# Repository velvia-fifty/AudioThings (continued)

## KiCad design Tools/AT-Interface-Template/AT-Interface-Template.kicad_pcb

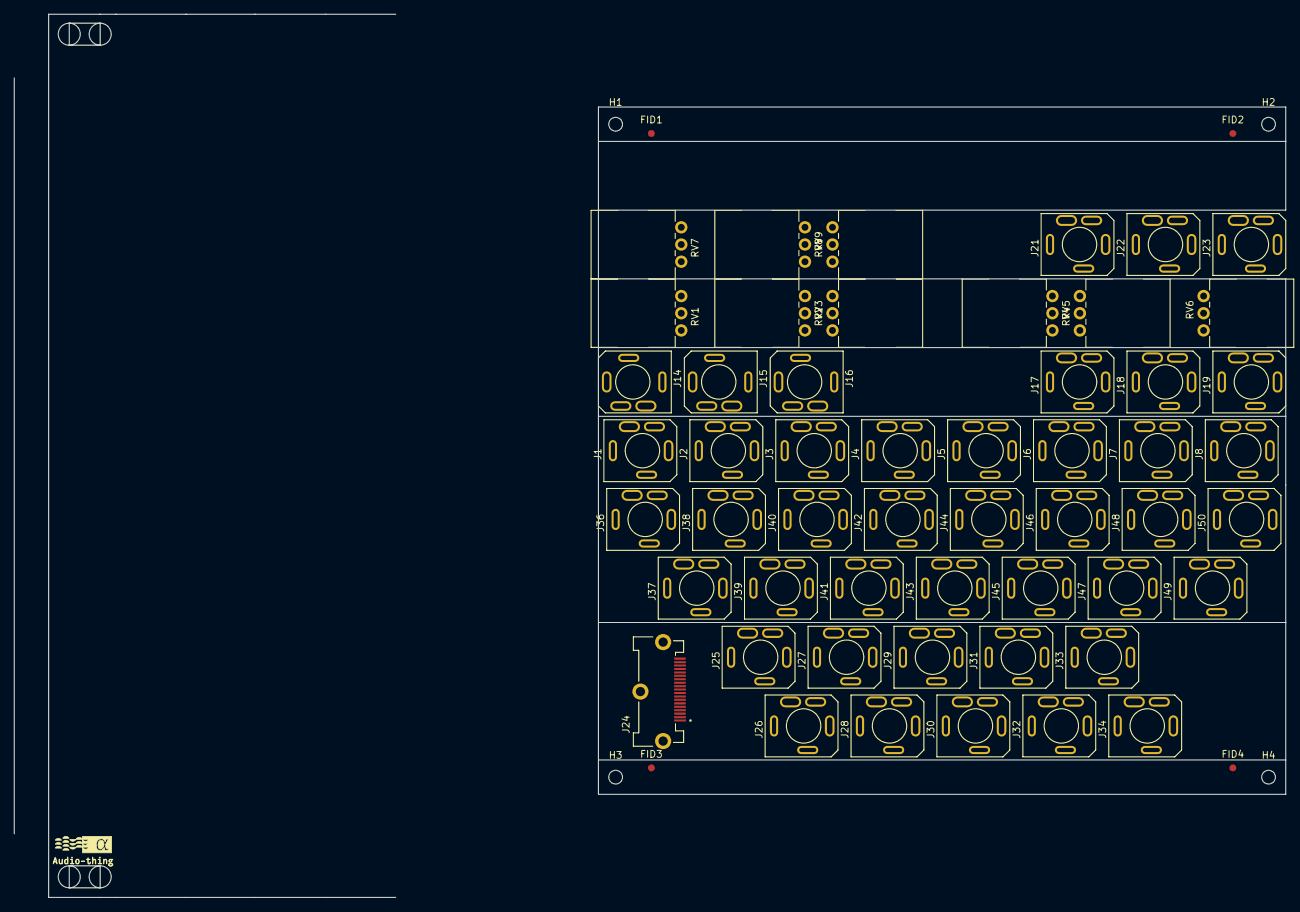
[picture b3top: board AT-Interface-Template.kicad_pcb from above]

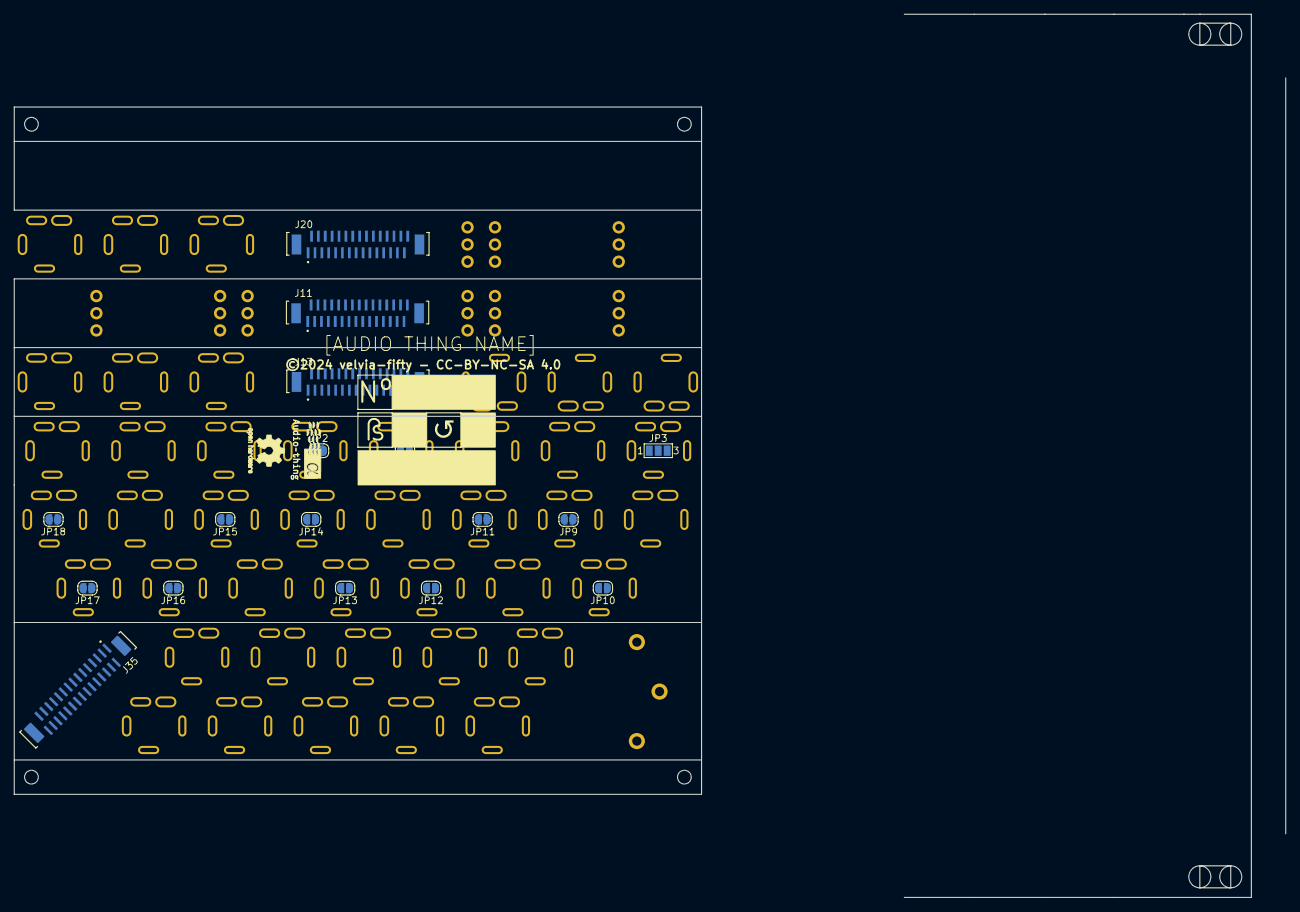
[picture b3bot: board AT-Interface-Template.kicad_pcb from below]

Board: 2 copper layers, 100.0 x 100.0 mm, 77 parts (17 on the bottom side), 102 nets, no tracks yet.

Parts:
FID1, FID2, FID3, FID4: Fiducial; Fiducial_1mm_Mask2mm
H1, H2, H3, H4: Tooling; MountingHole_2mm
J1, J2, J3, J4, J5, J6, J7, J8, J14, J15, J16, J17, J18, J19, J21, J22, J23, J36, J39, J42, J45, J48: IN; SJ3-3505
J11, J13, J20, J35: INT; ffc-30-v-TE_3-1734742-0
J24: HDMI; HDMI-v-PHOENIX_1332073
J25: 1; SJ3-3505
J26: 2; SJ3-3505
J27: 3; SJ3-3505
J28: 4; SJ3-3505
J29: 5; SJ3-3505
J30: 6; SJ3-3505
J31: 7; SJ3-3505
J32: 8; SJ3-3505
J33: 9; SJ3-3505
J34: M; SJ3-3505
J37, J40, J43, J46, J49: LEFT; SJ3-3505
J38, J41, J44, J47, J50: RIGHT; SJ3-3505
JP1: JOIN L; SolderJumper-2_P1.3mm_Open_RoundedPad1.0x1.5mm
JP2: JOIN R; SolderJumper-2_P1.3mm_Open_RoundedPad1.0x1.5mm
JP3: STEREO CONF; SolderJumper-3_P1.3mm_Open_Pad1.0x1.5mm_NumberLabels
JP9, JP10, JP11, JP12, JP13, JP14, JP15, JP16, JP17, JP18: DMONO; SolderJumper-2_P1.3mm_Open_RoundedPad1.0x1.5mm
RV1, RV2, RV3, RV4, RV5, RV6: PTV09 Pot V; 2HP_PTV09A-1_Single_Vertical
RV7, RV8, RV9: PTV09 Pot HZ; 2HP_PTV09A-1_Single_Vertical

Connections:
+12v: J11.1, J11.2, J13.1, J13.2, J20.1, J20.2, J35.1, J35.2
-12v: J11.29, J11.30, J13.29, J13.30, J20.29, J20.30, J35.29, J35.30
/ExtraMult/GND: J1.S, J2.S, J3.S, J4.S, J5.S, J6.S, J7.S, J8.S
/HDMI/R1: J24.2, J25.R, J35.5
/HDMI/R2: J24.4, J26.R, J35.9
/HDMI/R3: J24.6, J27.R, J35.13
/HDMI/R4: J24.8, J28.R, J35.16
/HDMI/R5: J24.10, J29.R, J35.20
/HDMI/R6: J24.12, J30.R, J35.24
/HDMI/R7: J24.14, J31.R
/HDMI/R8: J24.16, J32.R
/HDMI/R9: J24.18, J33.R
/HDMI/T1: J24.1, J25.T, J35.6
/HDMI/T2: J24.3, J26.T, J35.10
/HDMI/T3: J24.5, J27.T, J35.14
/HDMI/T4: J24.7, J28.T, J35.17
/HDMI/T5: J24.9, J29.T, J35.21
/HDMI/T6: J24.11, J30.T, J35.25
/HDMI/T7: J24.13, J31.T
/HDMI/T8: J24.15, J32.T
/HDMI/T9: J24.17, J33.T
/HDMI/T10: J24.19, J34.T
/Jacks/INT 1 - A: J13.5, J14.R
/Jacks/INT 1 - B: J13.6, J14.T
/Jacks/INT 1 - C: J13.7, J14.TN
/Jacks/INT 2 - A: J13.9, J15.R
/Jacks/INT 2 - B: J13.10, J15.T
/Jacks/INT 2 - C: J13.11, J15.TN
/Jacks/INT 3 - A: J13.13, J16.R
/Jacks/INT 3 - B: J13.14, J16.T
/Jacks/INT 3 - C: J13.15, J16.TN
/Jacks/INT 4 - A: J13.16, J17.R
/Jacks/INT 4 - B: J13.17, J17.T
/Jacks/INT 4 - C: J13.18, J17.TN
/Jacks/INT 5 - A: J13.20, J18.R
/Jacks/INT 5 - B: J13.21, J18.T
/Jacks/INT 5 - C: J13.22, J18.TN
/Jacks/INT 6 - A: J13.24, J19.R
/Jacks/INT 6 - B: J13.25, J19.T
/Jacks/INT 6 - C: J13.26, J19.TN
/Pot+Jack/INT 1 - A: J20.5, RV7.1
/Pot+Jack/INT 1 - B: J20.6, RV7.2
/Pot+Jack/INT 1 - C: J20.7, RV7.3
/Pot+Jack/INT 2 - A: J20.9, RV8.1
/Pot+Jack/INT 2 - B: J20.10, RV8.2
/Pot+Jack/INT 2 - C: J20.11, RV8.3
/Pot+Jack/INT 3 - A: J20.13, RV9.1
/Pot+Jack/INT 3 - B: J20.14, RV9.2
/Pot+Jack/INT 3 - C: J20.15, RV9.3
/Pot+Jack/INT 4 - A: J20.16, J21.R
/Pot+Jack/INT 4 - B: J20.17, J21.T
/Pot+Jack/INT 4 - C: J20.18, J21.TN
/Pot+Jack/INT 5 - A: J20.20, J22.R
/Pot+Jack/INT 5 - B: J20.21, J22.T
/Pot+Jack/INT 5 - C: J20.22, J22.TN
/Pot+Jack/INT 6 - A: J20.24, J23.R
/Pot+Jack/INT 6 - B: J20.25, J23.T
/Pot+Jack/INT 6 - C: J20.26, J23.TN
/Pots/INT 1 - A: J11.5, RV1.1
/Pots/INT 1 - B: J11.6, RV1.2
/Pots/INT 1 - C: J11.7, RV1.3
/Pots/INT 2 - A: J11.9, RV2.1
/Pots/INT 2 - B: J11.10, RV2.2
/Pots/INT 2 - C: J11.11, RV2.3
/Pots/INT 3 - A: J11.13, RV3.1
/Pots/INT 3 - B: J11.14, RV3.2
/Pots/INT 3 - C: J11.15, RV3.3
/Pots/INT 4 - A: J11.16, RV4.1
/Pots/INT 4 - B: J11.17, RV4.2
/Pots/INT 4 - C: J11.18, RV4.3
/Pots/INT 5 - A: J11.20, RV5.1
/Pots/INT 5 - B: J11.21, RV5.2
/Pots/INT 5 - C: J11.22, RV5.3
/Pots/INT 6 - A: J11.24, RV6.1
/Pots/INT 6 - B: J11.25, RV6.2
/Pots/INT 6 - C: J11.26, RV6.3
GND: J11.3, J11.4, J11.8, J11.12, J11.19, J11.23, J11.27, J11.28, J11.S1, J13.3, J13.4, J13.8, J13.12, J13.19, J13.23, J13.27, J13.28, J13.S1, J20.3, J20.4, J20.8, J20.12, J20.19, J20.23, J20.27, J20.28, J20.S1, J24.SH1, J24.SH2, J24.SH3, J25.S, J26.S, J27.S, J28.S, J29.S, J30.S, J31.S, J32.S, J33.S, J34.S, J35.3, J35.4, J35.8, J35.12, J35.19, J35.23, J35.27, J35.28, J35.S1, J36.S, J37.S, J38.S, J39.S, J40.S, J41.S, J42.S, J43.S, J44.S, J45.S, J46.S, J47.S, J48.S, J49.S, J50.S
unnamed: J5.T, J6.T, J7.T, J8.T, JP1.1 (A), JP3.1 (A)
unnamed: J1.T, J2.T, J3.T, J4.T, JP1.2 (B)
unnamed: J5.R, J6.R, J7.R, J8.R, JP2.1 (A)
unnamed: J2.R, J3.R, J4.R, JP2.2 (B), JP3.3 (B)
unnamed: J1.R, JP3.2 (C)
unnamed: J36.R, J38.T, JP9.1 (A)
unnamed: J38.R, JP9.2 (B)
unnamed: J36.T, J37.T, JP10.1 (A)
unnamed: J37.R, JP10.2 (B)
unnamed: J39.T, J40.T, JP11.1 (A)
unnamed: J40.R, JP11.2 (B)
unnamed: J39.R, J41.T, JP12.1 (A)
unnamed: J41.R, JP12.2 (B)
unnamed: J42.T, J43.T, JP13.1 (A)
unnamed: J43.R, JP13.2 (B)
unnamed: J42.R, J44.T, JP14.1 (A)
unnamed: J44.R, JP14.2 (B)
unnamed: J45.T, J46.T, JP15.1 (A)
unnamed: J46.R, JP15.2 (B)
unnamed: J45.R, J47.T, JP16.1 (A)
unnamed: J47.R, JP16.2 (B)
unnamed: J48.T, J49.T, JP17.1 (A)
unnamed: J49.R, JP17.2 (B)
unnamed: J48.R, J50.T, JP18.1 (A)
unnamed: J50.R, JP18.2 (B)

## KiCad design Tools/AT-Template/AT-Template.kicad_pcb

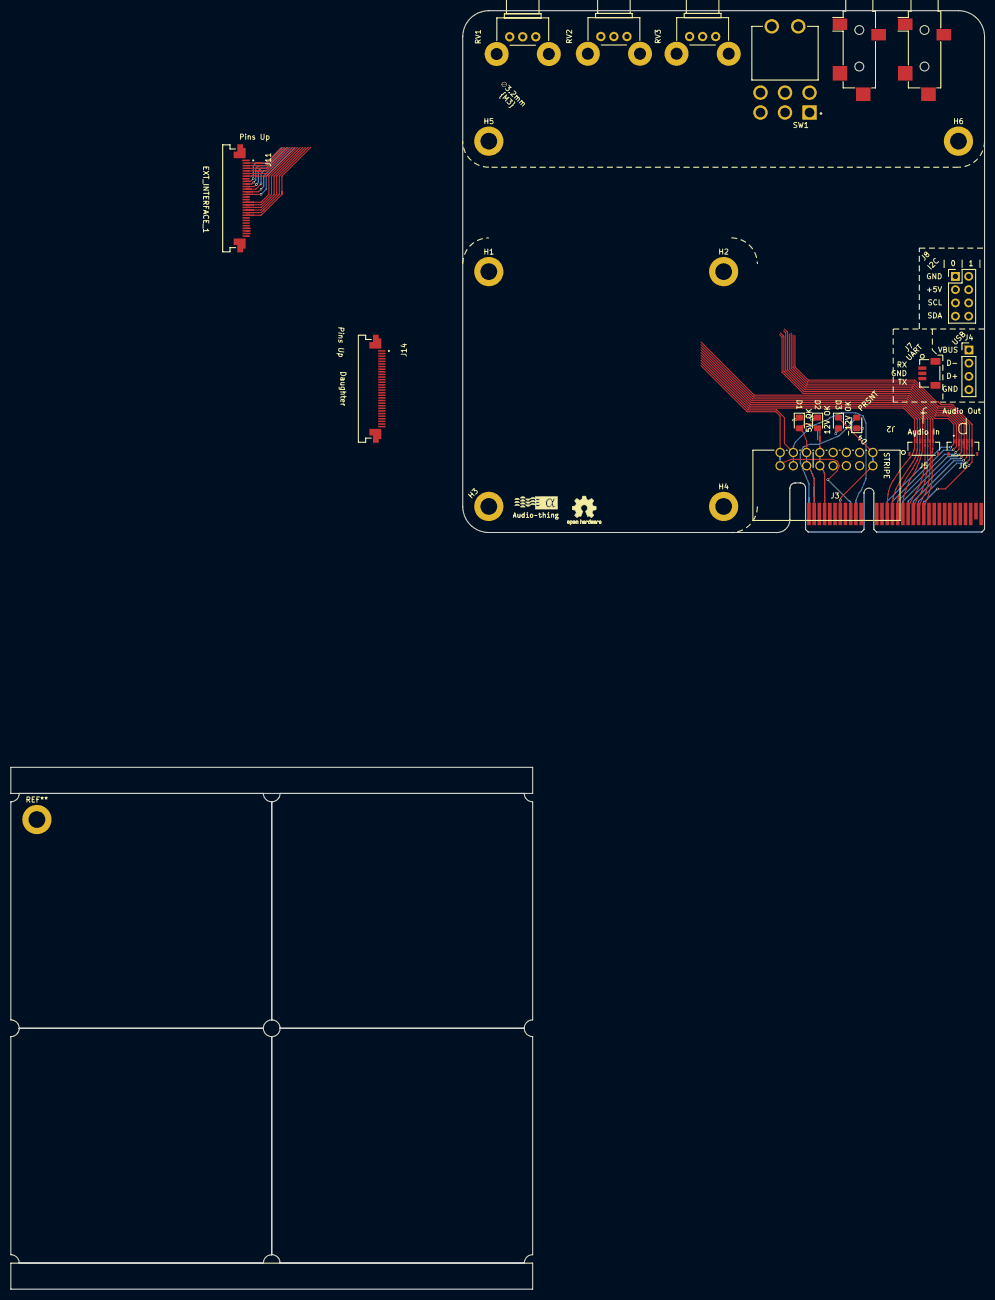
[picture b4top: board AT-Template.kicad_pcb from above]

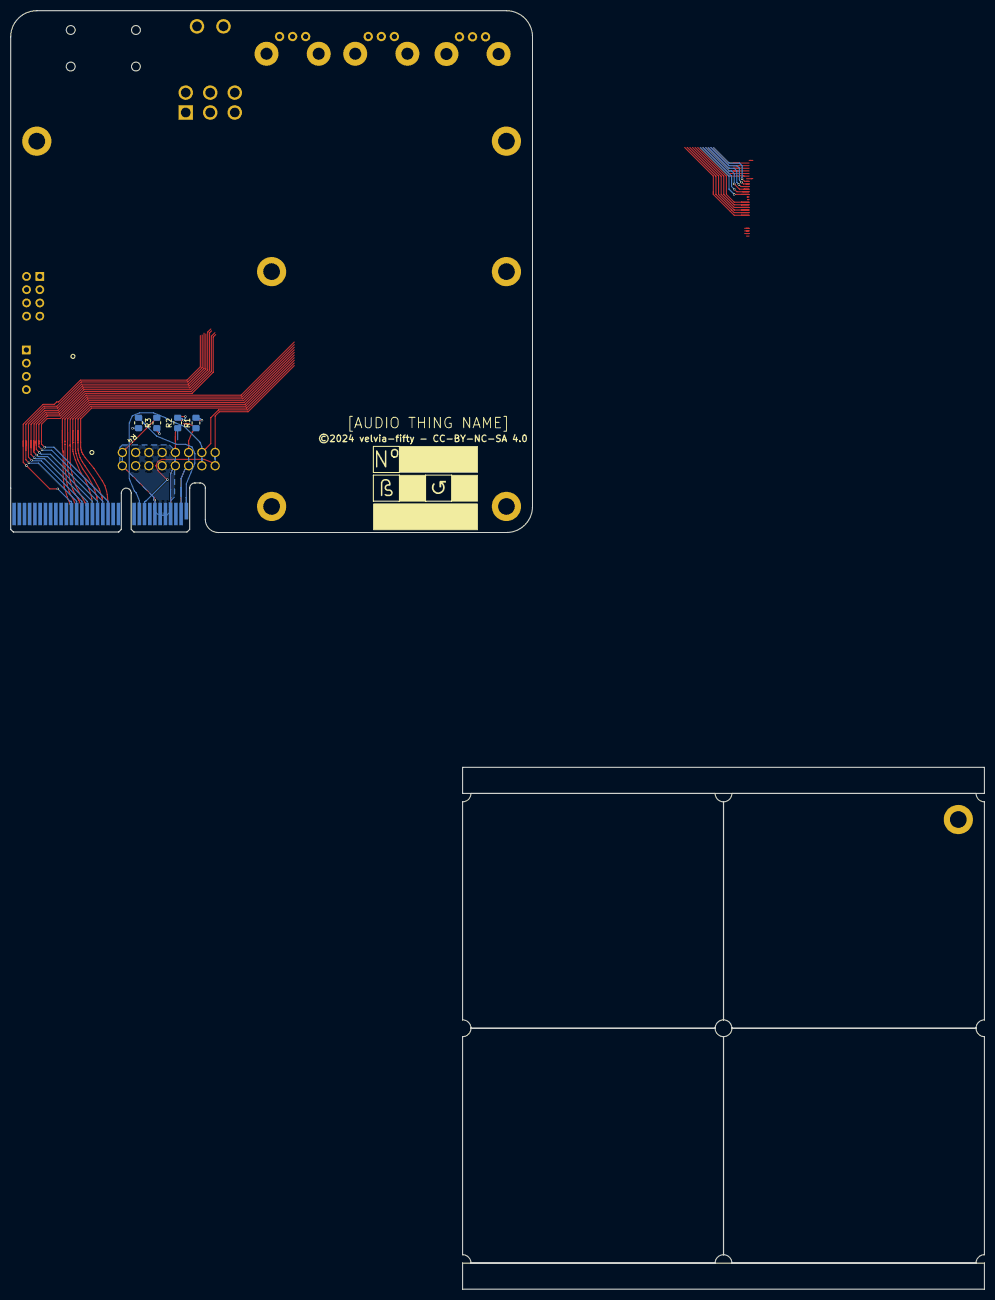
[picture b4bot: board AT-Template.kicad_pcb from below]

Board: 2 copper layers, 100.0 x 100.0 mm, 29 parts (4 on the bottom side), 29 nets.

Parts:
D1: 5V OK; LED_0805_2012Metric_Pad1.15x1.40mm_HandSolder
D2: 12V OK; LED_0805_2012Metric_Pad1.15x1.40mm_HandSolder
D3: -12V OK; LED_0805_2012Metric_Pad1.15x1.40mm_HandSolder
D4: PRSNT; LED_0805_2012Metric_Pad1.15x1.40mm_HandSolder
H1, H2, H3, H4, H5, H6: M3; MountingHole_3.2mm_M3_DIN965_Pad
J2: OPT EURO; EURORACK Right Angle
J3: BUS_PCIexpress_x4
J4: USB; PinHeader_1x04_P2.54mm_Vertical
J5: Audio In; AMPHENOL_F33B-1A7Q1-E8C08
J6: Audio Out; AMPHENOL_F33B-1A7Q1-E8C08
J7: UART; CONN_BM03B-SRSS-TBLFSN_JST
J8: I2C; PinHeader_2x04_P2.54mm_Vertical
J9, J10: Stereo Jack - SMD HZ; SMD_STEREO_CUI_SJ-3524-SMT_Horizontal
J11: EXT_INTERFACE_1; AMPHENOL_SFV30R-4STE1HLF - FFC - 30 RA
J14: Daughter; AMPHENOL_SFV30R-4STE1HLF - FFC - 30 RA
R1, R4: 150; R_0805_2012Metric_Pad1.20x1.40mm_HandSolder
R2, R3: 500; R_0805_2012Metric_Pad1.20x1.40mm_HandSolder
RV1, RV2, RV3: PTV09 Pot HZ; Potentiometer_Bourns_PTV09A-2_Single_Horizontal
SW1: Micro Toggle; DPDT Micro SW_1825138-7

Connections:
+5V: D1.2 (A), J2.11, J2.12, J3.A2 (+5V), J3.B2 (+5V), J8.3, J8.4
+12V: D2.2 (A), J2.9, J2.10, J3.A4 (+12V), J3.B4 (+12V)
-12V: D3.1 (K), J2.1, J2.2, J3.A7 (-12V), J3.B7 (-12V)
/Bus/CON_CV: J2.13, J2.14, J3.A10 (EURO_CV)
/Bus/CON_GATE: J2.15, J2.16, J3.A9 (EURO_GATE)
/Bus/I2C0_SCL: J3.B23 (I2C0_SCL), J8.5
/Bus/I2C0_SDA: J3.A24 (I2C0_SDA), J8.7
/Bus/I2C1_SCL: J3.A27 (I2C1_SCL), J8.6
/Bus/I2C1_SDA: J3.B27 (I2C1_SDA), J8.8
/Bus/USB_D+: J3.B12 (USB_D+), J4.3
GND: J2.3, J2.4, J2.5, J2.6, J2.7, J2.8, J3.A3 (GND), J3.A5 (GND), J3.A6 (GND), J3.A8 (GND), J3.A11 (GND), J3.A15 (GND), J3.A17 (GND), J3.A19 (GND), J3.A21 (GND), J3.A23 (GND), J3.A26 (GND), J3.B1 (GND), J3.B3 (GND), J3.B5 (GND), J3.B6 (GND), J3.B8 (GND), J3.B11 (GND), J3.B13 (GND), J3.B14 (GND), J3.B16 (GND), J3.B18 (GND), J3.B20 (GND), J3.B26 (GND), J3.B32 (GND), J4.4, J5.1, J5.3, J5.5, J5.7, J6.2, J6.4, J6.6, J6.8, J7.2, J8.1, J8.2, J11.1, J11.8, J11.15, J11.16, J11.23, J11.30, R1.1, R2.1, R3.2
unnamed: D1.1 (K), R1.2
unnamed: D2.1 (K), R2.2
unnamed: D3.2 (A), R3.1
unnamed: D4.2 (A), J3.B31 (PRSNT_B)
unnamed: D4.1 (K), R4.2
unnamed: J3.B15 (Audio_In_A), J5.2
unnamed: J3.B17 (Audio_In_B), J5.4
unnamed: J3.B19 (Audio_In_C), J5.6
unnamed: J3.B21 (Audio_In_D), J5.8
unnamed: J3.A14 (Audio_Out_A), J6.1
unnamed: J3.A16 (Audio_Out_B), J6.3
unnamed: J3.A18 (Audio_Out_C), J6.5
unnamed: J3.A20 (Audio_Out_D), J6.7
unnamed: J3.A1 (PRSNT_A), R4.1
unnamed: J3.B22 (UART_RX), J7.1
unnamed: J3.A22 (UART_TX), J7.3
unnamed: J3.A12 (USB_5V), J4.1
unnamed: J3.A13 (USB_D-), J4.2

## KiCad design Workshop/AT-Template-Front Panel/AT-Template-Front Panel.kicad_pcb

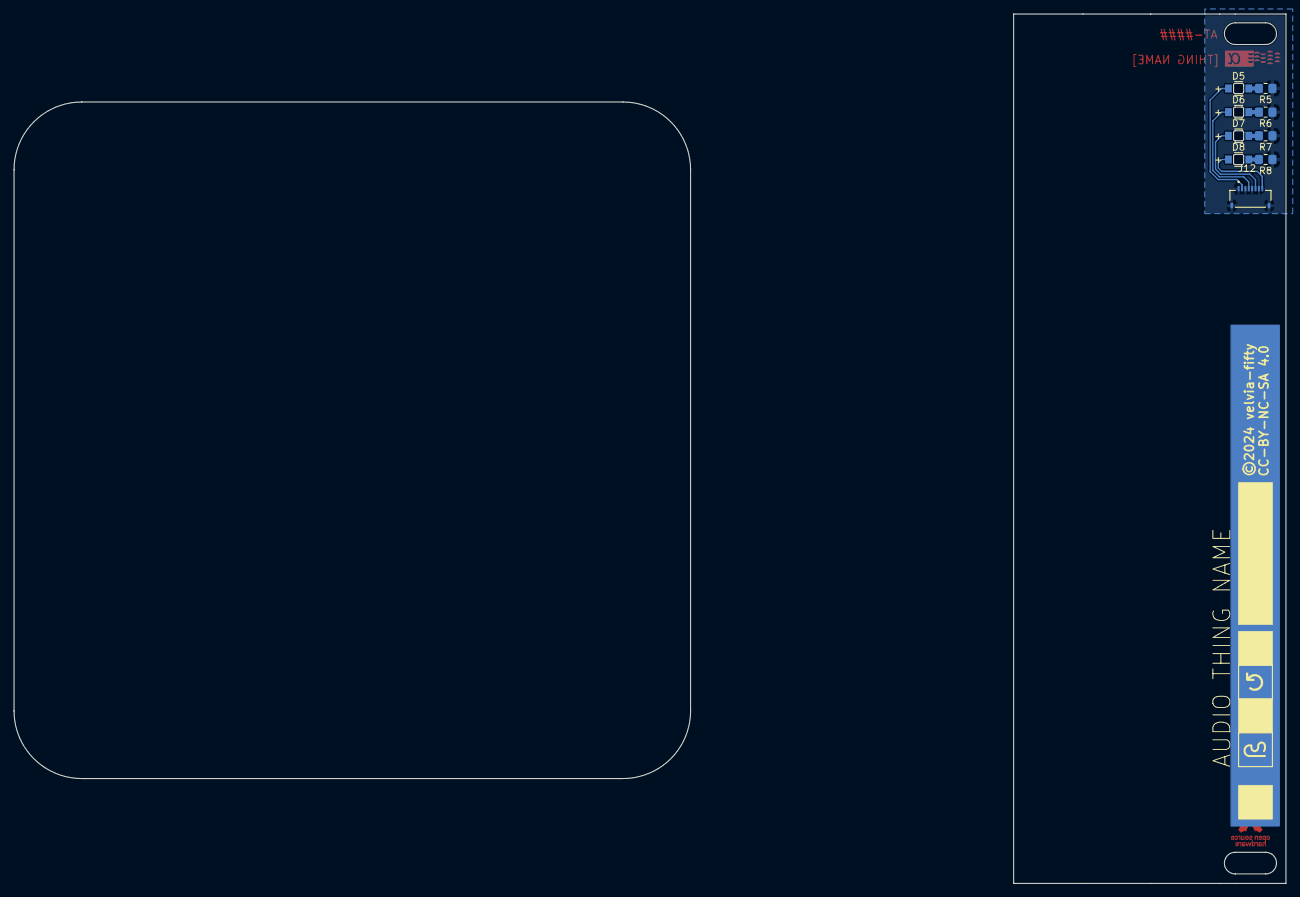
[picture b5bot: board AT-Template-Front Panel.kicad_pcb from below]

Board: 4 copper layers, 40.2 x 128.5 mm, 9 parts (5 on the bottom side), 9 nets.

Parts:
D5: LED (Red); WL-SMRD_1205
D6: LED (Yellow); WL-SMRD_1205
D7: LED (Green); WL-SMRD_1205
D8: LED (Blue); WL-SMRD_1205
J12: FRONT PANEL MAGIC; AMPHENOL_F33B-1A7Q1-E8C08
R5, R6, R7: 150R; R_0805_2012Metric_Pad1.20x1.40mm_HandSolder
R8: 100R; R_0805_2012Metric_Pad1.20x1.40mm_HandSolder

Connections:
GND: J12.1, J12.3, J12.5, J12.7, J12.SH1, J12.SH2, R5.1, R6.1, R7.1, R8.1
LED BLU: D8.2 (A), J12.8
LED GRN: D7.2 (A), J12.6
LED RED: D5.2 (A), J12.2
LED YLW: D6.2 (A), J12.4
unnamed: D5.1 (K), R5.2
unnamed: D6.1 (K), R6.2
unnamed: D7.1 (K), R7.2
unnamed: D8.1 (K), R8.2

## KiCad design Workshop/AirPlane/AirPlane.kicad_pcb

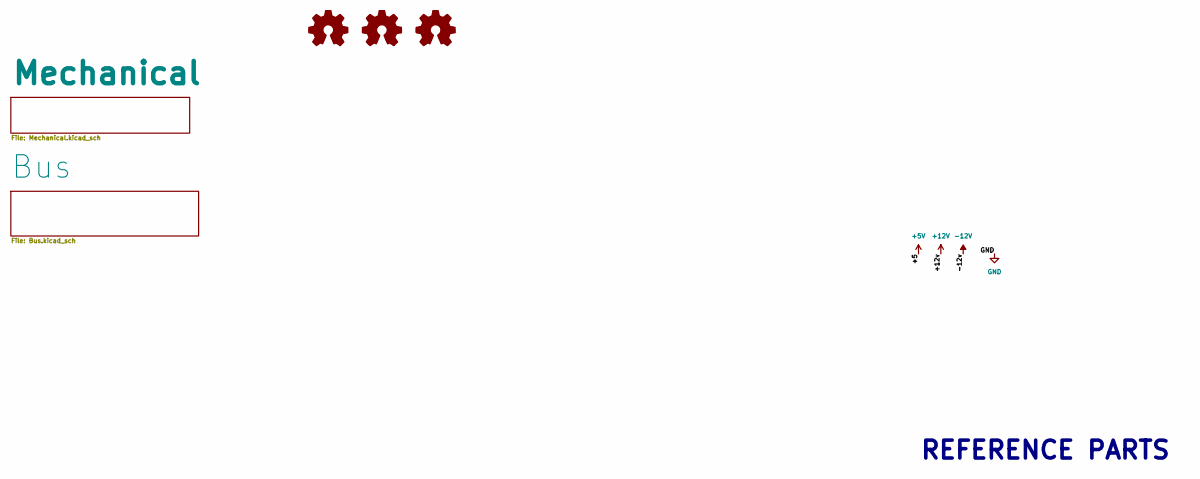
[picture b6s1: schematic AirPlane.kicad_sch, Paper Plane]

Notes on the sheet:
REFERENCE PARTS

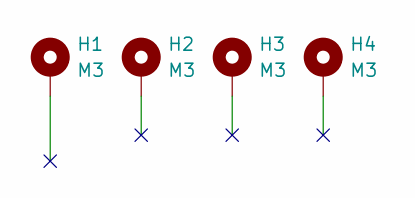
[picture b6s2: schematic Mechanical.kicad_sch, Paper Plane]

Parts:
H1, H2, H3, H4: M3; MountingHole_3.2mm_M3_DIN965_Pad

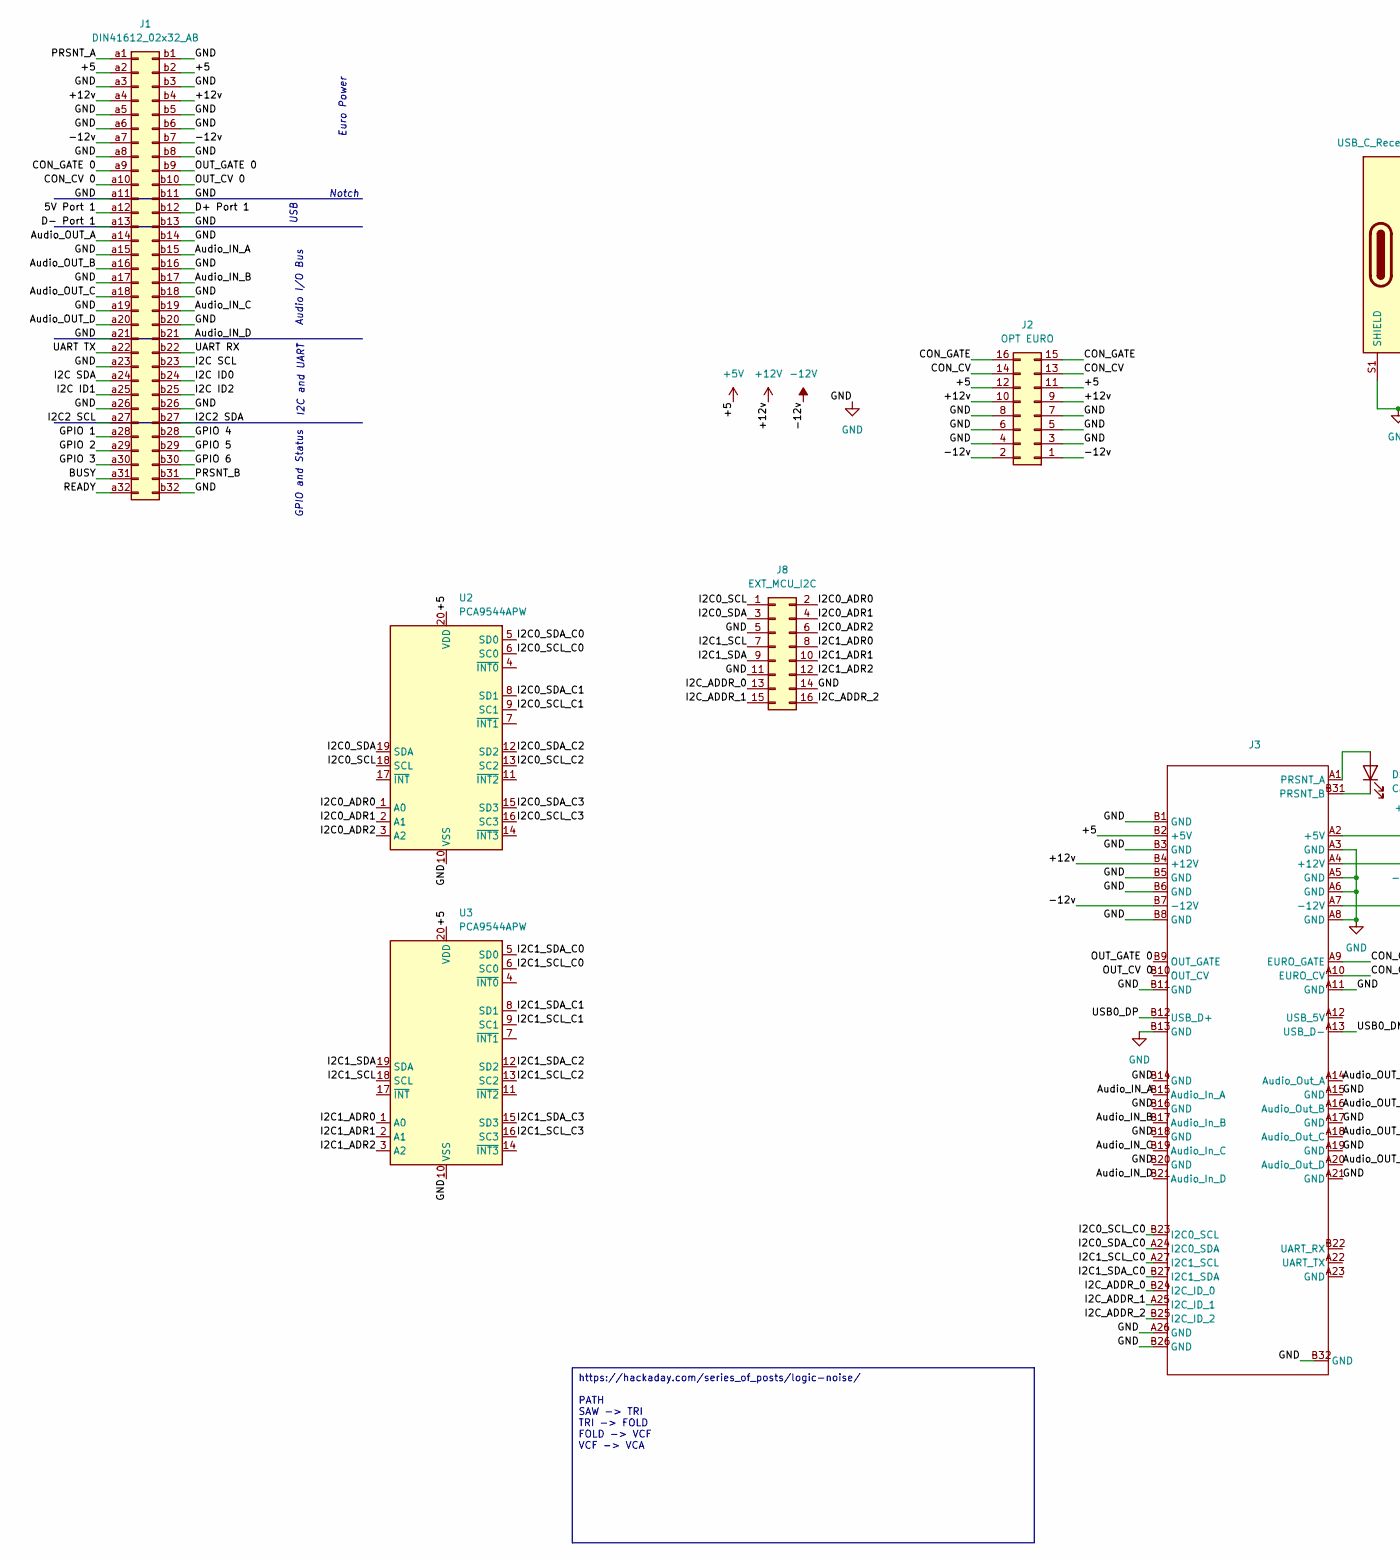
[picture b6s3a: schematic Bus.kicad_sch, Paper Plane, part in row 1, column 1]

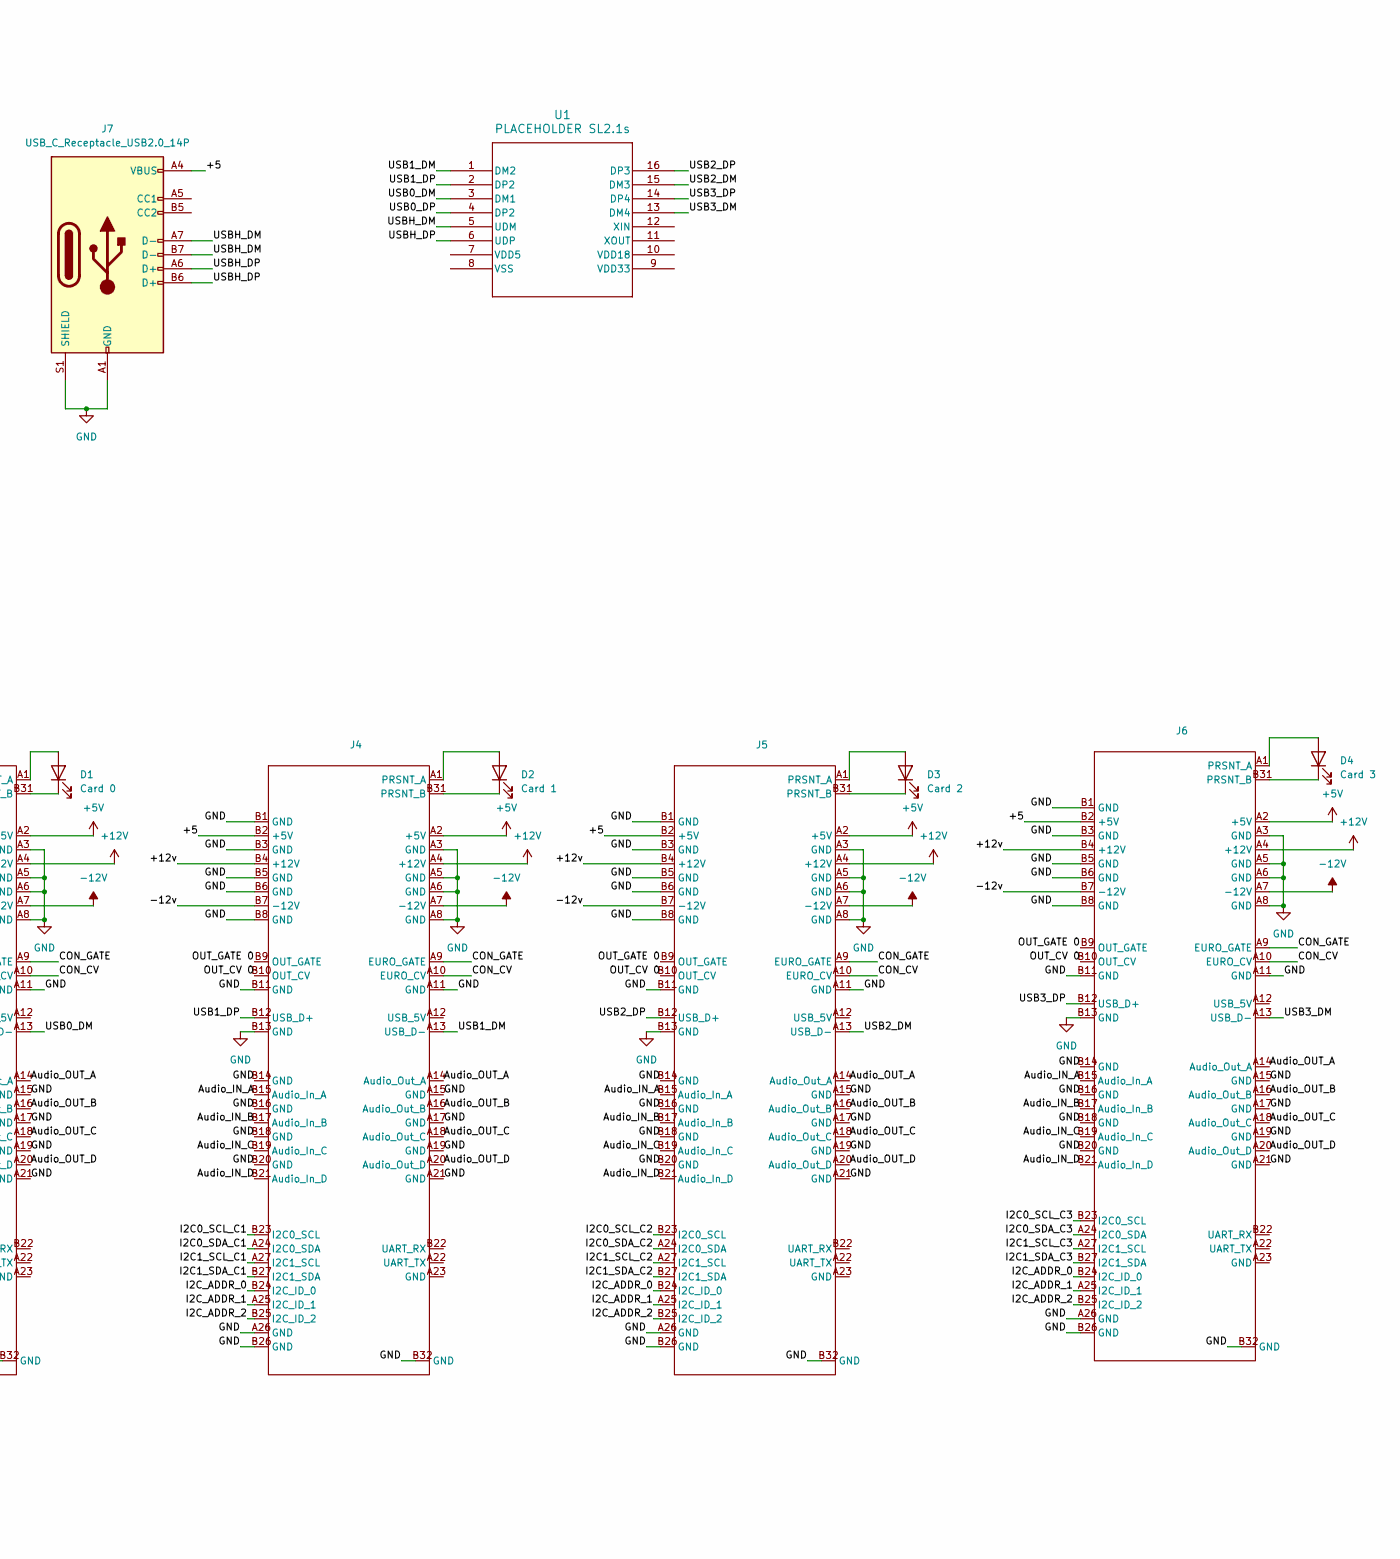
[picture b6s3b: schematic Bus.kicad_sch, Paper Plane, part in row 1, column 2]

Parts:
D1: Card 0; LED_0805_2012Metric_Pad1.15x1.40mm_HandSolder
D2: Card 1; LED_0805_2012Metric_Pad1.15x1.40mm_HandSolder
D3: Card 2; LED_0805_2012Metric_Pad1.15x1.40mm_HandSolder
D4: Card 3; LED_0805_2012Metric_Pad1.15x1.40mm_HandSolder
J1: DIN41612_02x32_AB
J2: OPT EURO; EURORACK Right Angle
J3, J4, J5, J6: PCIe x4 SMD AMPHENOL_10061913-111PLF
J7: USB_C_Receptacle_USB2.0_14P; USB_C_Receptacle_GCT_USB4105-xx-A_16P_TopMnt_Horizontal
J8: EXT_MCU_I2C; PinHeader_2x08_P2.54mm_Vertical
U1: PLACEHOLDER SL2.1s; SSOP-16_3.9x4.9mm_P0.635mm
U2, U3: PCA9544APW; TSSOP-20_4.4x6.5mm_P0.65mm

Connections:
+5V: J1.a2, J1.b2, J2.11, J2.12, J3.A2 (+5V), J3.B2 (+5V), J4.A2 (+5V), J4.B2 (+5V), J5.A2 (+5V), J5.B2 (+5V), J6.A2 (+5V), J6.B2 (+5V), J7.A4 (VBUS), J7.A9 (VBUS), J7.B4 (VBUS), J7.B9 (VBUS), U2.20 (VDD), U3.20 (VDD)
+12V: J1.a4, J1.b4, J2.9, J2.10, J3.A4 (+12V), J3.B4 (+12V), J4.A4 (+12V), J4.B4 (+12V), J5.A4 (+12V), J5.B4 (+12V), J6.A4 (+12V), J6.B4 (+12V)
-12V: J1.a7, J1.b7, J2.1, J2.2, J3.A7 (-12V), J3.B7 (-12V), J4.A7 (-12V), J4.B7 (-12V), J5.A7 (-12V), J5.B7 (-12V), J6.A7 (-12V), J6.B7 (-12V)
/Bus/Audio_IN_A: J1.b15, J3.B15 (Audio_In_A), J4.B15 (Audio_In_A), J5.B15 (Audio_In_A), J6.B15 (Audio_In_A)
/Bus/Audio_IN_B: J1.b17, J3.B17 (Audio_In_B), J4.B17 (Audio_In_B), J5.B17 (Audio_In_B), J6.B17 (Audio_In_B)
/Bus/Audio_IN_C: J1.b19, J3.B19 (Audio_In_C), J4.B19 (Audio_In_C), J5.B19 (Audio_In_C), J6.B19 (Audio_In_C)
/Bus/Audio_IN_D: J1.b21, J3.B21 (Audio_In_D), J4.B21 (Audio_In_D), J5.B21 (Audio_In_D), J6.B21 (Audio_In_D)
/Bus/Audio_OUT_A: J1.a14, J3.A14 (Audio_Out_A), J4.A14 (Audio_Out_A), J5.A14 (Audio_Out_A), J6.A14 (Audio_Out_A)
/Bus/Audio_OUT_B: J1.a16, J3.A16 (Audio_Out_B), J4.A16 (Audio_Out_B), J5.A16 (Audio_Out_B), J6.A16 (Audio_Out_B)
/Bus/Audio_OUT_C: J1.a18, J3.A18 (Audio_Out_C), J4.A18 (Audio_Out_C), J5.A18 (Audio_Out_C), J6.A18 (Audio_Out_C)
/Bus/Audio_OUT_D: J1.a20, J3.A20 (Audio_Out_D), J4.A20 (Audio_Out_D), J5.A20 (Audio_Out_D), J6.A20 (Audio_Out_D)
/Bus/CON_CV: J2.13, J2.14, J3.A10 (EURO_CV), J4.A10 (EURO_CV), J5.A10 (EURO_CV), J6.A10 (EURO_CV)
/Bus/CON_GATE: J2.15, J2.16, J3.A9 (EURO_GATE), J4.A9 (EURO_GATE), J5.A9 (EURO_GATE), J6.A9 (EURO_GATE)
/Bus/I2C0_ADR0: J8.2, U2.1 (A0)
/Bus/I2C0_ADR1: J8.4, U2.2 (A1)
/Bus/I2C0_ADR2: J8.6, U2.3 (A2)
/Bus/I2C0_SCL: J8.1, U2.18 (SCL)
/Bus/I2C0_SCL_C0: J3.B23 (I2C0_SCL), U2.6 (SC0)
/Bus/I2C0_SCL_C1: J4.B23 (I2C0_SCL), U2.9 (SC1)
/Bus/I2C0_SCL_C2: J5.B23 (I2C0_SCL), U2.13 (SC2)
/Bus/I2C0_SCL_C3: J6.B23 (I2C0_SCL), U2.16 (SC3)
/Bus/I2C0_SDA: J8.3, U2.19 (SDA)
/Bus/I2C0_SDA_C0: J3.A24 (I2C0_SDA), U2.5 (SD0)
/Bus/I2C0_SDA_C1: J4.A24 (I2C0_SDA), U2.8 (SD1)
/Bus/I2C0_SDA_C2: J5.A24 (I2C0_SDA), U2.12 (SD2)
/Bus/I2C0_SDA_C3: J6.A24 (I2C0_SDA), U2.15 (SD3)
/Bus/I2C1_ADR0: J8.8, U3.1 (A0)
/Bus/I2C1_ADR1: J8.10, U3.2 (A1)
/Bus/I2C1_ADR2: J8.12, U3.3 (A2)
/Bus/I2C1_SCL: J8.7, U3.18 (SCL)
/Bus/I2C1_SCL_C0: J3.A27 (I2C1_SCL), U3.6 (SC0)
/Bus/I2C1_SCL_C1: J4.A27 (I2C1_SCL), U3.9 (SC1)
/Bus/I2C1_SCL_C2: J5.A27 (I2C1_SCL), U3.13 (SC2)
/Bus/I2C1_SCL_C3: J6.A27 (I2C1_SCL), U3.16 (SC3)
/Bus/I2C1_SDA: J8.9, U3.19 (SDA)
/Bus/I2C1_SDA_C0: J3.B27 (I2C1_SDA), U3.5 (SD0)
/Bus/I2C1_SDA_C1: J4.B27 (I2C1_SDA), U3.8 (SD1)
/Bus/I2C1_SDA_C2: J5.B27 (I2C1_SDA), U3.12 (SD2)
/Bus/I2C1_SDA_C3: J6.B27 (I2C1_SDA), U3.15 (SD3)
/Bus/I2C_ADDR_0: J3.B24 (I2C_ID_0), J4.B24 (I2C_ID_0), J5.B24 (I2C_ID_0), J6.B24 (I2C_ID_0), J8.13
/Bus/I2C_ADDR_1: J3.A25 (I2C_ID_1), J4.A25 (I2C_ID_1), J5.A25 (I2C_ID_1), J6.A25 (I2C_ID_1), J8.15
/Bus/I2C_ADDR_2: J3.B25 (I2C_ID_2), J4.B25 (I2C_ID_2), J5.B25 (I2C_ID_2), J6.B25 (I2C_ID_2), J8.16
/Bus/OUT_CV 0: J1.b10, J3.B10 (OUT_CV), J4.B10 (OUT_CV), J5.B10 (OUT_CV), J6.B10 (OUT_CV)
/Bus/OUT_GATE 0: J1.b9, J3.B9 (OUT_GATE), J4.B9 (OUT_GATE), J5.B9 (OUT_GATE), J6.B9 (OUT_GATE)
/Bus/USB0_DM: J3.A13 (USB_D-), U1.3 (DM1)
/Bus/USB0_DP: J3.B12 (USB_D+), U1.4 (DP2)
/Bus/USB1_DM: J4.A13 (USB_D-), U1.1 (DM2)
/Bus/USB1_DP: J4.B12 (USB_D+), U1.2 (DP2)
/Bus/USB2_DM: J5.A13 (USB_D-), U1.15 (DM3)
/Bus/USB2_DP: J5.B12 (USB_D+), U1.16 (DP3)
/Bus/USB3_DM: J6.A13 (USB_D-), U1.13 (DM4)
/Bus/USB3_DP: J6.B12 (USB_D+), U1.14 (DP4)
/Bus/USBH_DM: J7.A7 (D-), J7.B7 (D-), U1.5 (UDM)
/Bus/USBH_DP: J7.A6 (D+), J7.B6 (D+), U1.6 (UDP)
GND: J1.a3, J1.a5, J1.a6, J1.a8, J1.a11, J1.a15, J1.a17, J1.a19, J1.a21, J1.a23, J1.a26, J1.b1, J1.b3, J1.b5, J1.b6, J1.b8, J1.b11, J1.b13, J1.b14, J1.b16, J1.b18, J1.b20, J1.b26, J1.b32, J2.3, J2.4, J2.5, J2.6, J2.7, J2.8, J3.A3 (GND), J3.A5 (GND), J3.A6 (GND), J3.A8 (GND), J3.A11 (GND), J3.A15 (GND), J3.A17 (GND), J3.A19 (GND), J3.A21 (GND), J3.A26 (GND), J3.B1 (GND), J3.B3 (GND), J3.B5 (GND), J3.B6 (GND), J3.B8 (GND), J3.B11 (GND), J3.B13 (GND), J3.B14 (GND), J3.B16 (GND), J3.B18 (GND), J3.B20 (GND), J3.B26 (GND), J3.B32 (GND), J4.A3 (GND), J4.A5 (GND), J4.A6 (GND), J4.A8 (GND), J4.A11 (GND), J4.A15 (GND), J4.A17 (GND), J4.A19 (GND), J4.A21 (GND), J4.A26 (GND), J4.B1 (GND), J4.B3 (GND), J4.B5 (GND), J4.B6 (GND), J4.B8 (GND), J4.B11 (GND), J4.B13 (GND), J4.B14 (GND), J4.B16 (GND), J4.B18 (GND), J4.B20 (GND), J4.B26 (GND), J4.B32 (GND), J5.A3 (GND), J5.A5 (GND), J5.A6 (GND), J5.A8 (GND), J5.A11 (GND), J5.A15 (GND), J5.A17 (GND), J5.A19 (GND), J5.A21 (GND), J5.A26 (GND), J5.B1 (GND), J5.B3 (GND), J5.B5 (GND), J5.B6 (GND), J5.B8 (GND), J5.B11 (GND), J5.B13 (GND), J5.B14 (GND), J5.B16 (GND), J5.B18 (GND), J5.B20 (GND), J5.B26 (GND), J5.B32 (GND), J6.A3 (GND), J6.A5 (GND), J6.A6 (GND), J6.A8 (GND), J6.A11 (GND), J6.A15 (GND), J6.A17 (GND), J6.A19 (GND), J6.A21 (GND), J6.A26 (GND), J6.B1 (GND), J6.B3 (GND), J6.B5 (GND), J6.B6 (GND), J6.B8 (GND), J6.B11 (GND), J6.B13 (GND), J6.B14 (GND), J6.B16 (GND), J6.B18 (GND), J6.B20 (GND), J6.B26 (GND), J6.B32 (GND), J7.A1 (GND), J7.A12 (GND), J7.B1 (GND), J7.B12 (GND), J7.S1 (SHIELD), J8.5, J8.11, J8.14, U2.10 (VSS), U3.10 (VSS)
unnamed: D1.2 (A), J3.A1 (PRSNT_A)
unnamed: D1.1 (K), J3.B31 (PRSNT_B)
unnamed: D2.2 (A), J4.A1 (PRSNT_A)
unnamed: D2.1 (K), J4.B31 (PRSNT_B)
unnamed: D3.2 (A), J5.A1 (PRSNT_A)
unnamed: D3.1 (K), J5.B31 (PRSNT_B)
unnamed: D4.2 (A), J6.A1 (PRSNT_A)
unnamed: D4.1 (K), J6.B31 (PRSNT_B)

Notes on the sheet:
https://hackaday.com/series_of_posts/logic-noise/ PATH SAW -> TRI TRI -> FOLD FOLD -> VCF VCF -> VCA
Audio I/O Bus
USB
Notch
Euro Power
GPIO and Status
I2C and UART

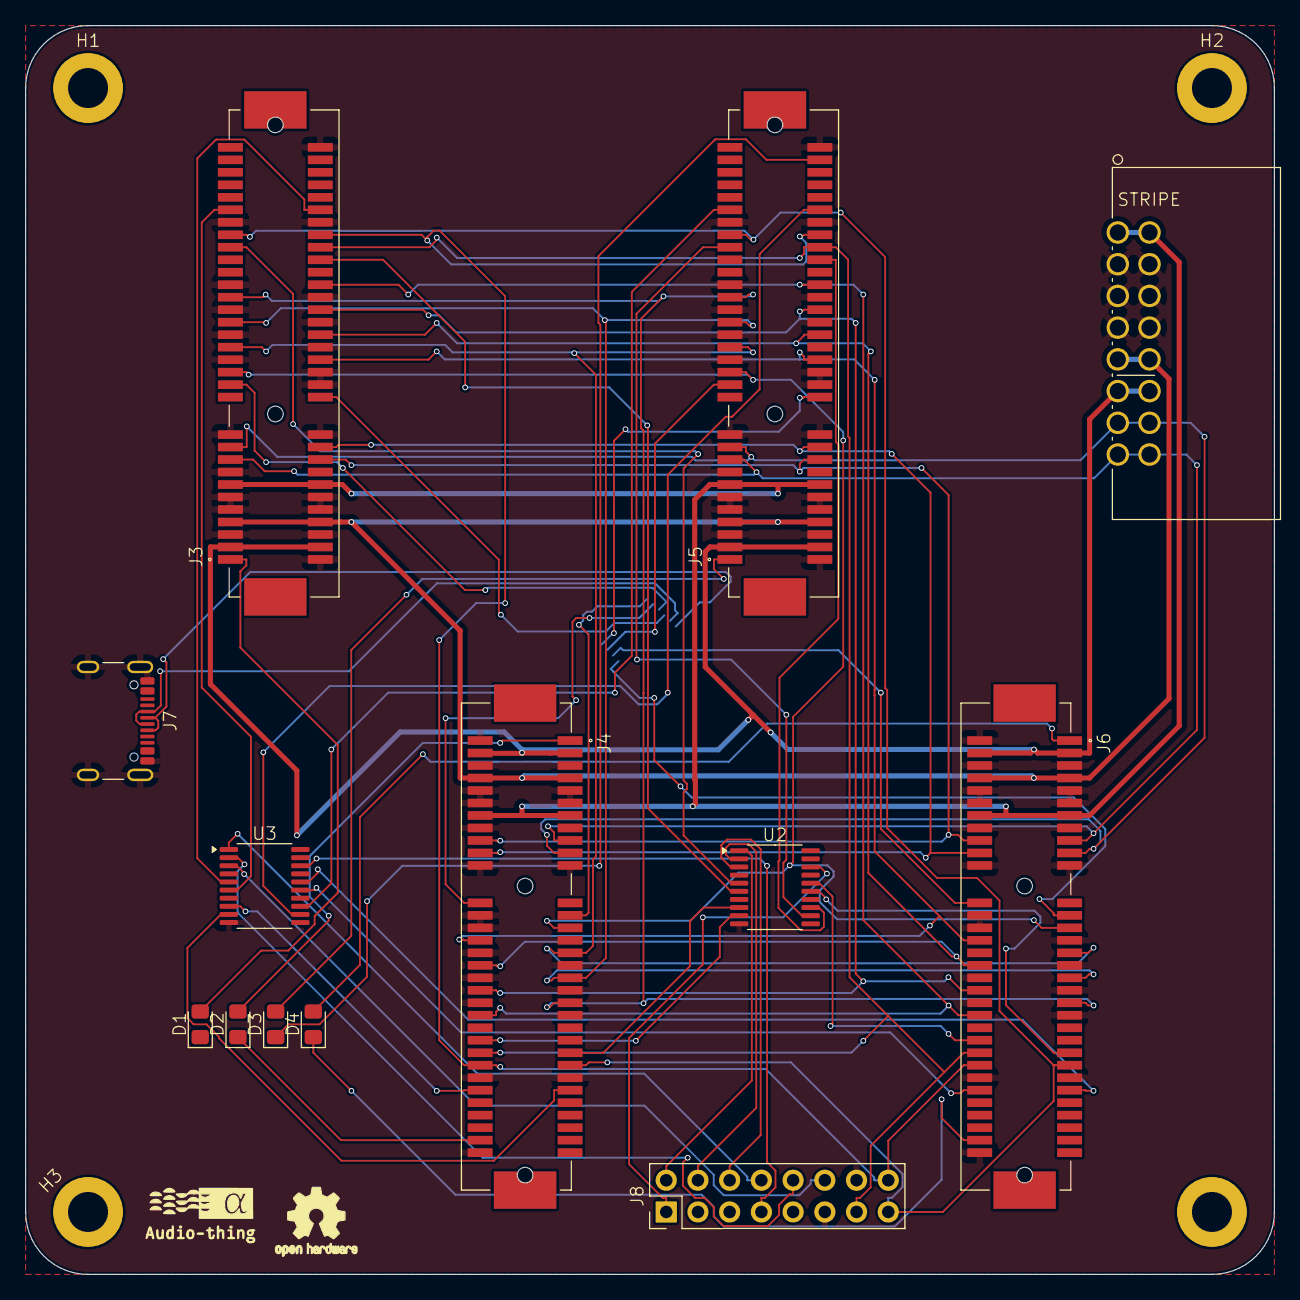
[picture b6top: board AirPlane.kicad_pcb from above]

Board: 2 copper layers, 100.0 x 100.0 mm, 18 parts (1 on the bottom side), 63 nets.
